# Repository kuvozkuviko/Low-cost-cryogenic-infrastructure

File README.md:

# Low-Cost Cryogenic Infrastructure

**EPFL Quantum Science and Engineering — Semester Project 2025–2026**  
**Author:** Andrés Quesnel González  
**Supervisor:** Dr. Gregor Taylor  
**Professor:** Prof. Edoardo Charbon

A low-cost cryogenic temperature readout system based on the Lake Shore Cryotronics DT-670 silicon diode and a thermal load measurement PCB for characterising the heat dissipation of 
cryogenic electronics.

---

## Overview

The system provides a stable 10 µA excitation current to a DT-670 silicon diode, reads the resulting voltage with a 24-bit ADC, converts it to temperature using the manufacturer's calibration 
table, and displays the result on two 7-segment displays. It was validated by monitoring the 4 K and 40 K stages of a Photon Spot Cryospot 4 over 24 hours.

The companion thermal load PCB uses a 1 kΩ thin-film resistor as a controllable heat source to establish a calibration curve of the cryocooler's cooling capacity as a function of temperature. 
This curve can then be used to quantify the thermal impact of any electronics placed inside the cryostat.

---

## Hardware

### Temperature Readout PCB

A custom PCB (60 × 35 mm) that drives a DT-670 silicon diode with a stable 10 µA constant current and reads its voltage response via a 24-bit ADS1220 ADC. 
The converted temperature is shown on two Grove 4-digit 7-segment displays connected to an Arduino UNO R4 WiFi.

**Key components:**

| Component | Part | Purpose |
|---|---|---|
| Voltage shunt regulator | LM4041-N ADJ | Precision 1.225 V reference |
| Transistor array | THAT 320S14-U | PNP current source with thermal compensation |
| Sensing resistor | TNPW0603 66.5 kΩ (0.1%, 10 PPM/°C) | Sets output current to 10 µA |
| ADC | ADS1220 | 24-bit, 596 nV resolution with 5 V reference |
| Voltage regulator | LM78L05 | 5 V regulated supply from 12 V lab rail |
| Microcontroller | Arduino UNO R4 WiFi | Reads ADC via SPI, drives displays |
| Displays | Grove 4-digit 7-segment (TM1637) | Shows temperature in kelvin |
| Connector | L17HTNES4R2C (Amphenol, right-angle DB-9) | Interfaces with cryostat wiring |

**Temperature resolution:**  
20 µK at 4 K · 259 µK at 300 K  
(24-bit ADC at 5 V reference, diode sensitivity from Table 2 of the report)

**Total system cost: CHF 273.26**

### Thermal Load PCB

A minimal PCB (16.24 × 15.26 mm) with a single 1 kΩ thin-film resistor, M3 mounting hole, and 4-pin through-hole connector for 4-wire SMU connection. 
It attaches to the PCB under test on one side and to a copper puck on the other.

---

## Getting Started

### Arduino Firmware

#### Requirements

- Arduino IDE 2.x or later
- Libraries (install via Library Manager):
  - `ADS1220_WE` by Wolfgang Ewald
  - `TM1637Display` by Avishay Orpaz

#### Wiring

| ADS1220 pin | Arduino UNO R4 pin |
|---|---|
| CS | 7 |
| DRDY | 6 |
| SCLK | 13 (SPI SCK) |
| DIN | 11 (SPI MOSI) |
| DOUT | 12 (SPI MISO) |

| Display | CLK | DIO |
|---|---|---|
| Sensor 1 (4 K stage) | 2 | 3 |
| Sensor 2 (40 K stage) | 4 | 5 |

---

### Python — Data Acquisition

Reads the Arduino's serial output and saves it to a CSV file.

#### Requirements

```
pip install pyserial
```

#### Usage

```bash
python code/data_Sidiode.py --port /dev/ttyUSB0 --output CSVs/andres_2_06_log_temperaturereadout.csv
```

Arguments:
- `--port`: Serial port the Arduino is connected to (e.g. `COM3` on Windows, `/dev/ttyACM0` on Linux)
- `--output`: Path to the output CSV file
- `--baud`: Baud rate (default: 9600)

Output CSV format:
```
time_ms, T1_K, T2_K
1204, 3.214823, 32.771456
...
```

---

### Python — Analysis and Plotting

#### Requirements

```
pip install numpy pandas matplotlib scipy
```

#### Temperature curves (RT measurement)

```bash
python Code/Sidiode_plot.py --input CSVs/andres_2_06_log_temperaturereadout.csv
```

Produces a plot of temperature vs time for both stages, equivalent to Figure 8 in the report.

#### Thermal load calibration curves

```bash
python python/analysis/plot_heatload.py \
    --smooth data/heatload_smooth.csv \
    --coarse data/heatload_coarse.csv
```

Produces the three-panel plot (Figure 9 in the report): measured power vs temperature, power difference vs temperature, and cryogenic resistance R(T).

Input CSV format (from the AQUA lab measurement script):
```
Time [s], T [K], Current [A], Voltage [V], Power [mW], Resistance [Ohm]
```

---

## Mechanical

`Thermal Load/CopperPuck-Body.step` is the STEP file for the copper puck used to absorb heat on the back side of the thermal load PCB when it is mounted inside the cryostat. Import into FreeCAD, Fusion 360, or any STEP-compatible CAD tool.

---

## SPICE Simulation

`Temperature Readout/Simu_SiDiode670.asc` is the LTspice XVII simulation of the LM4041-N ADJ constant current source. It was used to verify that the output current is independent of the biasing current and to compare the performance of the 120 kΩ and 122.5 kΩ sensing resistor values.

Open with LTspice XVII (free, from Analog Devices).

---

## Bill of Materials

| Item | Cost (CHF) |
|---|---|
| PCB fabrication (Eurocircuits) | 200.00 |
| Arduino UNO R4 WiFi | 23.70 |
| 2× Grove 7-segment displays | 13.77 |
| Display cables | 1.10 |
| Stripboard | 5.10 |
| Aluminium enclosure (Hammond) | 25.30 |
| **Total** | **269.97** |

---

## Known Issues and Future Work

- The 66.5 kΩ sensing resistor was hand-soldered to replace the original 120 kΩ value. The solder joints are visually imperfect and the output current may deviate slightly from the target 10 µA, introducing a small systematic temperature offset.
- The DB-9 connector pin ordering on the original PCB was incorrect and was corrected with a wired adapter. A future PCB revision should use the correct pinout directly.
- The ADS1220 is configured with a 5 V external reference (REFP0 = 5 V), giving 596 nV resolution. Using the internal 2.048 V reference would improve resolution to 244 nV, since the DT-670 voltage never exceeds 1.644 V.
- Two-minute dwell times between thermal load current steps were insufficient for full thermal equilibration. Future measurements should use at least 5 minutes per step.
- The thermal load calibration was performed with the PCB under test powered off. A future measurement with the PCB powered will yield its actual heat dissipation.

---

## Related Files

The full semester project report (`TP4_spring_2026.pdf`) is included at the root of this repository and contains the full circuit analysis, component selection rationale, measurement results, and discussion.

---

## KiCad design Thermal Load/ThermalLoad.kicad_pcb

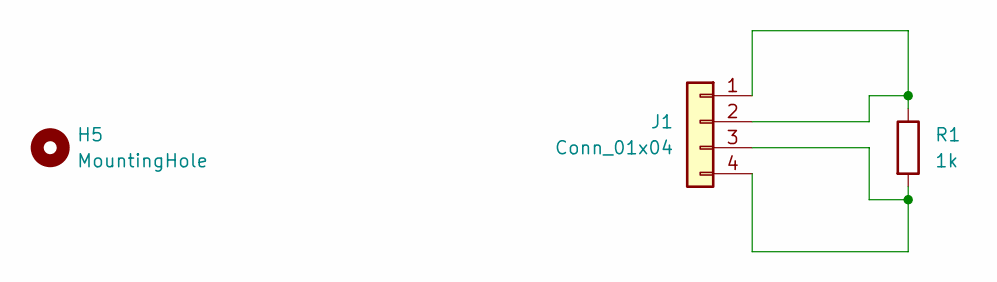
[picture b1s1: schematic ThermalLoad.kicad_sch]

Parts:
H5: MountingHole; MountingHole_3.2mm_M3
J1: Conn_01x04; PinHeader_1x04_P2.54mm_Vertical
R1: 1k; R_0603_1608Metric

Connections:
unnamed: J1.1, J1.2, R1.1
unnamed: J1.3, J1.4, R1.2

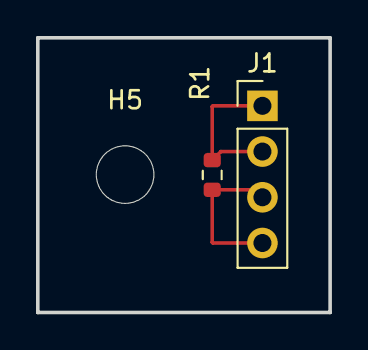
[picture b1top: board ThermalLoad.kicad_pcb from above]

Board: 2 copper layers, 16.2 x 15.3 mm, 3 parts (0 on the bottom side), 2 nets.

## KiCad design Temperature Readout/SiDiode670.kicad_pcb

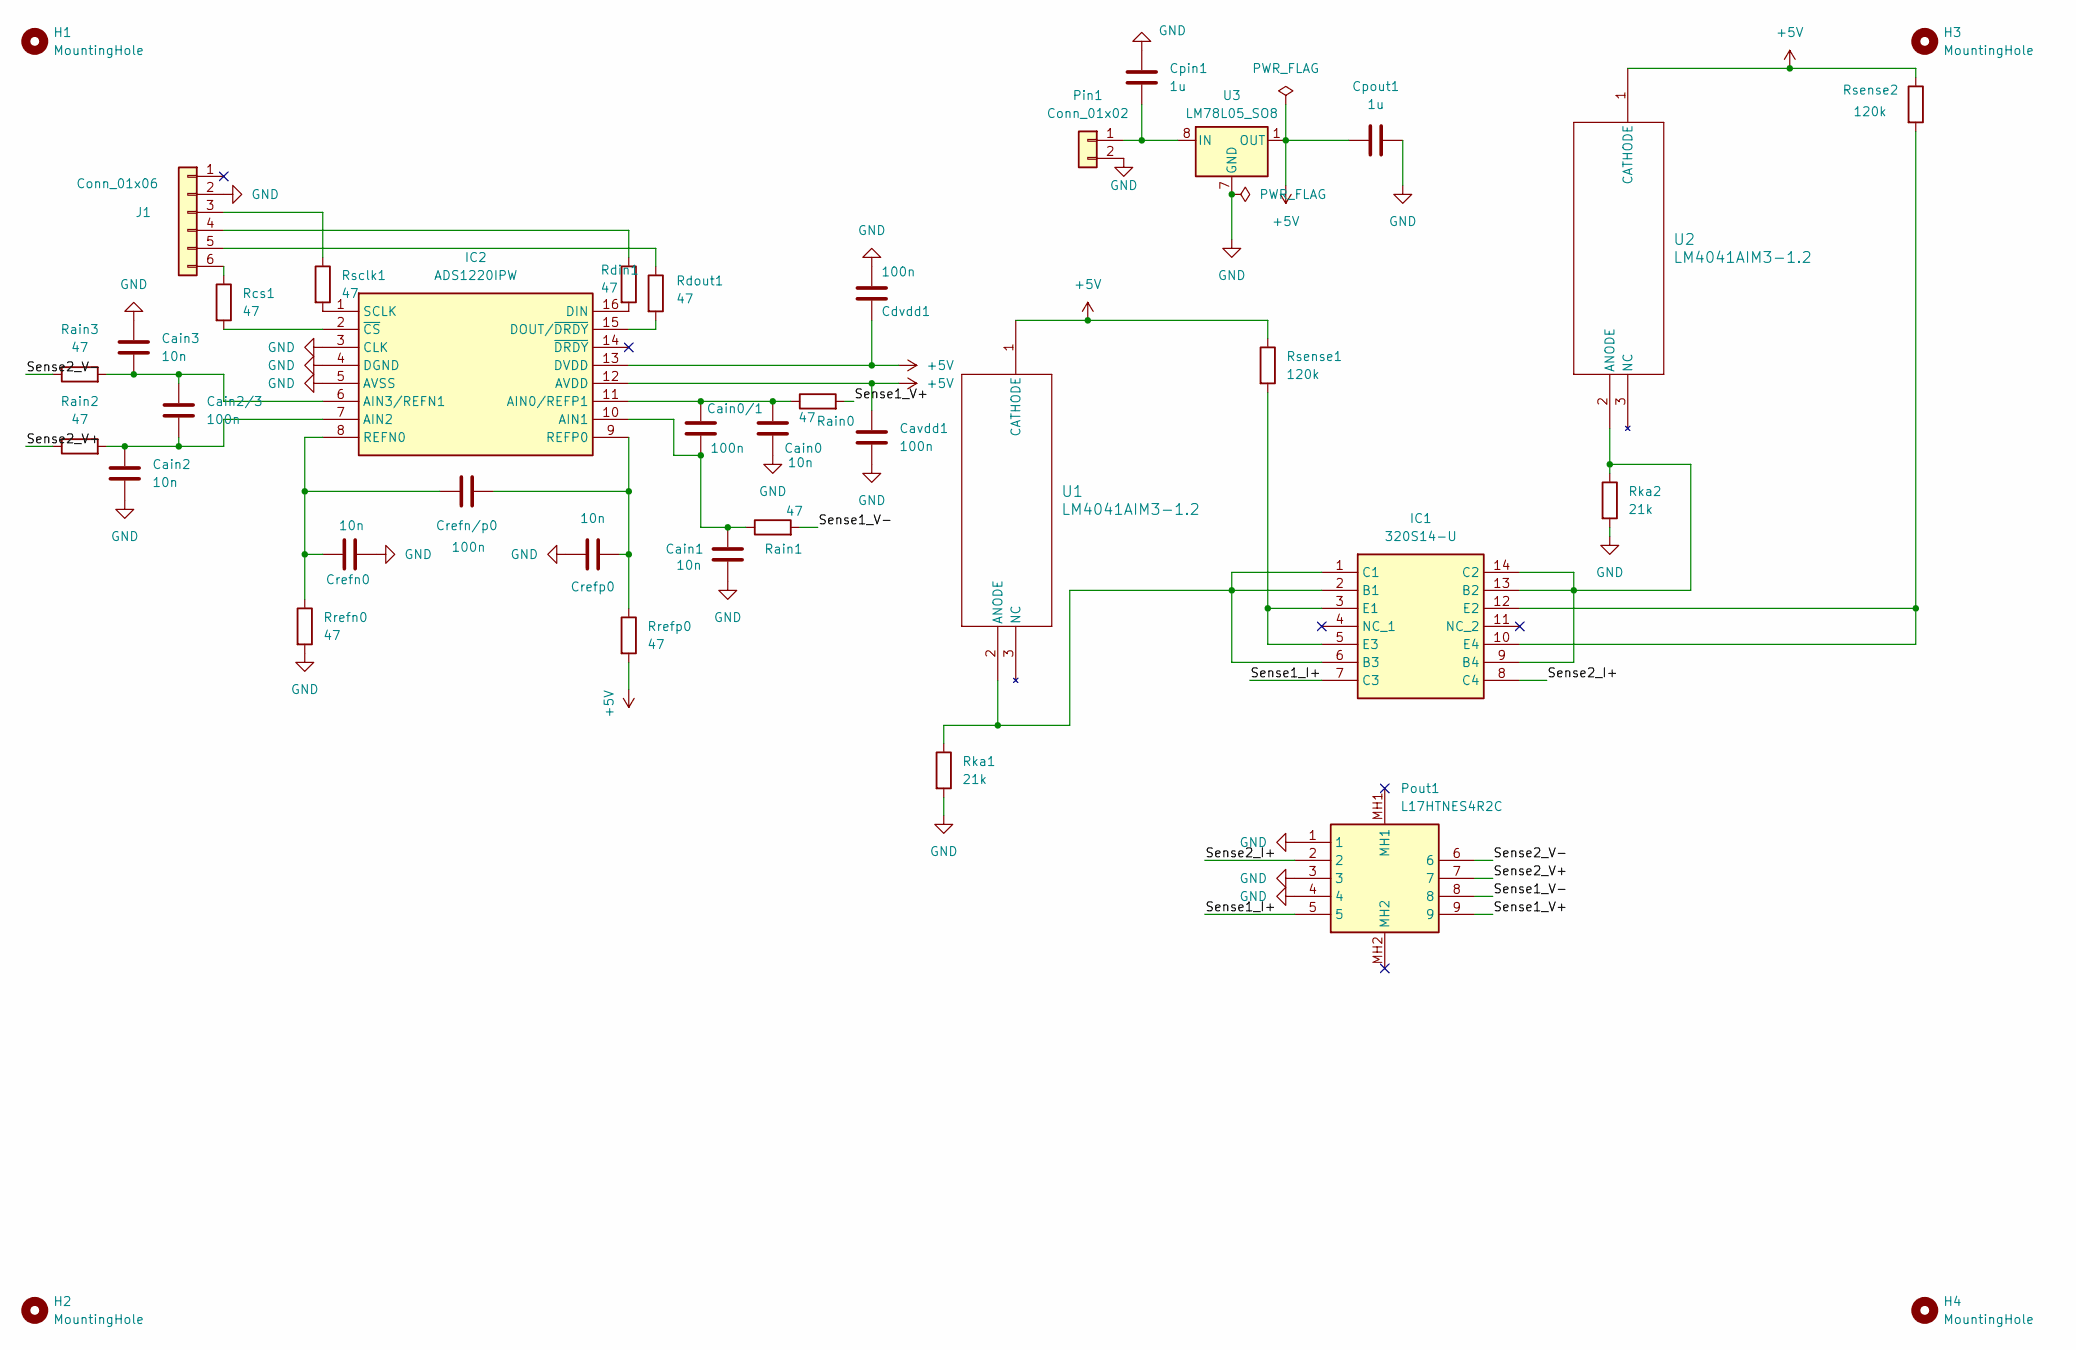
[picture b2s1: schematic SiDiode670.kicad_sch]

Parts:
Cain0, Cain1, Cain2, Cain3: 10n; C_0603_1608Metric
Cain0/1, Cain2/3: 100n; C_1206_3216Metric
Cavdd1: 100n; C_0603_1608Metric
Cdvdd1: 100n; C_0603_1608Metric
Cpin1: 1u; C_0603_1608Metric
Cpout1: 1u; C_0603_1608Metric
Crefn0: 10n; C_0603_1608Metric
Crefn/p0: 100n; C_1206_3216Metric
Crefp0: 10n; C_0603_1608Metric
H1, H2, H3, H4: MountingHole; MountingHole_3.2mm_M3
IC1: 320S14-U; SOIC127P602X175-14N; Mouser Part Number 887-320S14-U
IC2: ADS1220IPW; SOP65P640X120-16N; Mouser Part Number 595-ADS1220IPW
J1: Conn_01x06; PinHeader_1x06_P2.54mm_Vertical
Pin1: Conn_01x02; PinHeader_1x02_P2.54mm_Vertical
Pout1: L17HTNES4R2C; Mouser Part Number 523-L17HTNES4R2C
Rain0, Rain1, Rain2, Rain3: 47; R_0603_1608Metric
Rcs1: 47; R_0603_1608Metric
Rdin1: 47; R_0603_1608Metric
Rdout1: 47; R_0603_1608Metric
Rka1, Rka2: 21k; R_0603_1608Metric
Rrefn0: 47; R_0603_1608Metric
Rrefp0: 47; R_0603_1608Metric
Rsclk1: 47; R_0603_1608Metric
Rsense1, Rsense2: 120k; R_0603_1608Metric
U1, U2: LM4041AIM3-1.2; SOT-23_DBZ_TEX-L
U3: LM78L05_SO8; SOIC-8_3.9x4.9mm_P1.27mm

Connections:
+5V: Cavdd1.1, Cdvdd1.1, Cpout1.1, IC2.12 (AVDD), IC2.13 (DVDD), Rrefp0.2, Rsense1.1, Rsense2.1, U1.1 (CATHODE), U2.1 (CATHODE), U3.1 (OUT)
/Sense1_I+: IC1.7 (C3), Pout1.5
/Sense1_V+: Pout1.9, Rain0.2
/Sense1_V-: Pout1.8, Rain1.2
/Sense2_I+: IC1.8 (C4), Pout1.2
/Sense2_V+: Pout1.7, Rain2.1
/Sense2_V-: Pout1.6, Rain3.1
GND: Cain0.2, Cain1.2, Cain2.2, Cain3.1, Cavdd1.2, Cdvdd1.2, Cpin1.1, Cpout1.2, Crefn0.2, Crefp0.1, IC2.3 (CLK), IC2.4 (DGND), IC2.5 (AVSS), J1.2, Pin1.2, Pout1.1, Pout1.3, Pout1.4, Rka1.2, Rka2.2, Rrefn0.2, U3.2 (GND), U3.3 (GND), U3.6 (GND), U3.7 (GND)
unnamed: IC1.1 (C1), IC1.2 (B1), IC1.6 (B3), Rka1.1, U1.2 (ANODE)
unnamed: IC1.9 (B4), IC1.13 (B2), IC1.14 (C2), Rka2.1, U2.2 (ANODE)
unnamed: IC1.3 (E1), IC1.5 (E3), Rsense1.2
unnamed: IC1.10 (E4), IC1.12 (E2), Rsense2.2
unnamed: Cain0.1, Cain0/1.1, IC2.11 (AIN0/REFP1), Rain0.1
unnamed: Cain0/1.2, Cain1.1, IC2.10 (AIN1), Rain1.1
unnamed: Cain2.1, Cain2/3.2, IC2.7 (AIN2), Rain2.2
unnamed: Cain2/3.1, Cain3.2, IC2.6 (AIN3/REFN1), Rain3.2
unnamed: IC2.16 (DIN), Rdin1.2
unnamed: IC2.15 (DOUT/~DRDY), Rdout1.2
unnamed: Crefn0.1, Crefn/p0.1, IC2.8 (REFN0), Rrefn0.1
unnamed: Crefn/p0.2, Crefp0.2, IC2.9 (REFP0), Rrefp0.1
unnamed: IC2.1 (SCLK), Rsclk1.2
unnamed: IC2.2 (~CS), Rcs1.2
unnamed: J1.3, Rsclk1.1
unnamed: J1.4, Rdin1.1
unnamed: J1.5, Rdout1.1
unnamed: J1.6, Rcs1.1
unnamed: Cpin1.2, Pin1.1, U3.8 (IN)

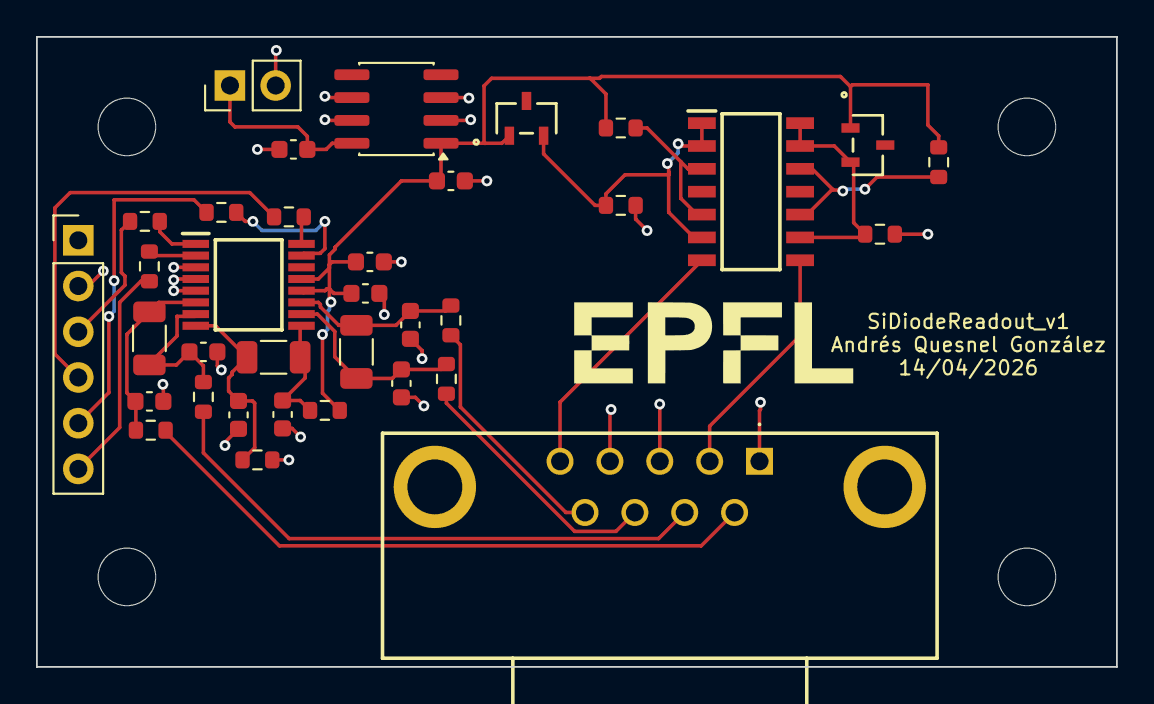
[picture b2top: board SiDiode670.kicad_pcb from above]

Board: 2 copper layers, 60.0 x 35.0 mm, 39 parts (0 on the bottom side), 27 nets.

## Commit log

2026-06-07 Create Temperature Readout
2026-06-07 Create Thermal Load
